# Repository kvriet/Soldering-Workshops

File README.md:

# Soldering Workshops

1. Wireless LEDs

2. Lighthouse

3. Moduli

4. LED cube

5. Lotus

6. Controller

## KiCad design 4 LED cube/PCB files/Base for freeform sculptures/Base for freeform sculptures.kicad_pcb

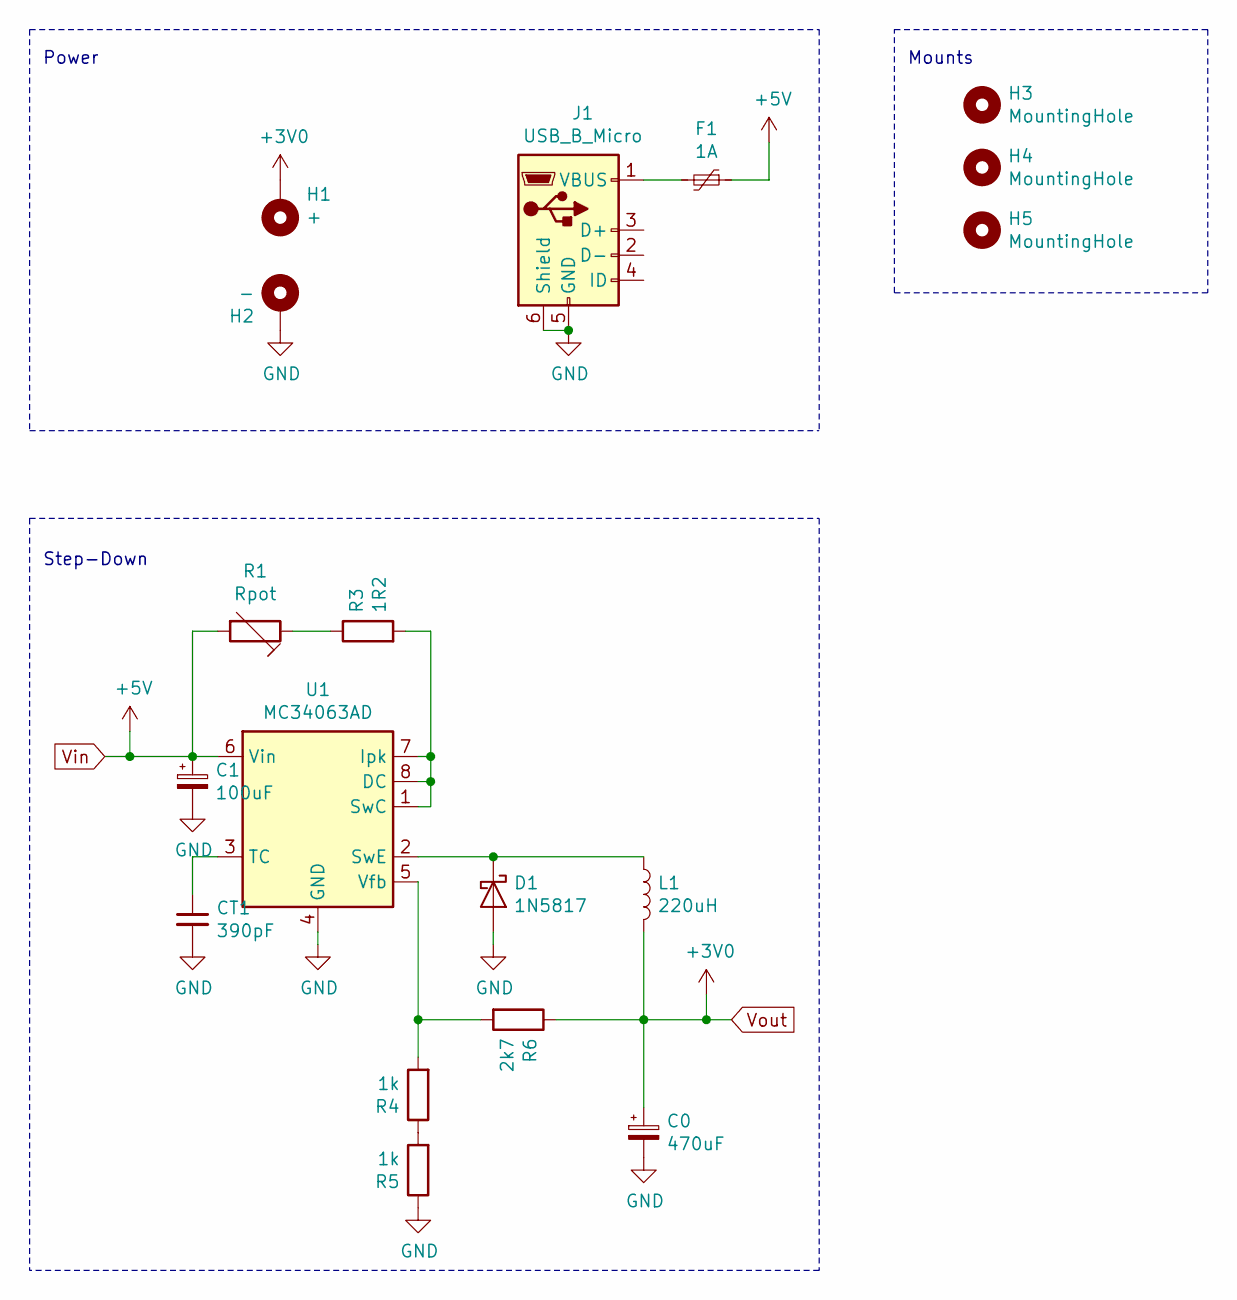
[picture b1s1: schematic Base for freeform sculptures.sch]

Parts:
C0: 470uF; CP_Radial_D10.0mm_P5.00mm
C1: 100uF; CP_Radial_D6.3mm_P2.50mm
CT1: 390pF; C_Disc_D4.3mm_W1.9mm_P5.00mm
D1: 1N5817; D_A-405_P10.16mm_Horizontal
F1: 1A; Fuse_Littelfuse_395Series
H1: +; Pin_D1.0mm_L10.0mm
H2: -; Pin_D1.0mm_L10.0mm
H3, H4, H5: MountingHole; Pin_D1.0mm_L10.0mm
J1: USB_B_Micro; USB_Micro-B_MC-026
L1: 220uH; L_Radial_D7.5mm_P5.00mm_Fastron_07P
R1: Rpot; Potentiometer_Bourns_3386P_Vertical
R3: 1R2; R_Axial_DIN0207_L6.3mm_D2.5mm_P10.16mm_Horizontal
R4, R5: 1k; R_Axial_DIN0207_L6.3mm_D2.5mm_P10.16mm_Horizontal
R6: 2k7; R_Axial_DIN0207_L6.3mm_D2.5mm_P10.16mm_Horizontal
U1: MC34063AD; DIP-8_W7.62mm_Socket_LongPads

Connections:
GND: C0.2, C1.2, CT1.2, D1.2 (A), H2.1, J1.5 (GND), J1.6 (Shield), R5.1, U1.4 (GND)
unnamed: CT1.1, U1.3 (TC)
unnamed: D1.1 (K), L1.1, U1.2 (SwE)
unnamed: F1.2, J1.1 (VBUS)
unnamed: R1.1, R3.1
unnamed: R3.2, U1.1 (SwC), U1.7 (Ipk), U1.8 (DC)
unnamed: R4.1, R5.2
unnamed: R4.2, R6.2, U1.5 (Vfb)
Vin: C1.1, F1.1, R1.2, U1.6 (Vin)
Vout: C0.1, H1.1, L1.2, R6.1

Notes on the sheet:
Power
Mounts
Step-Down

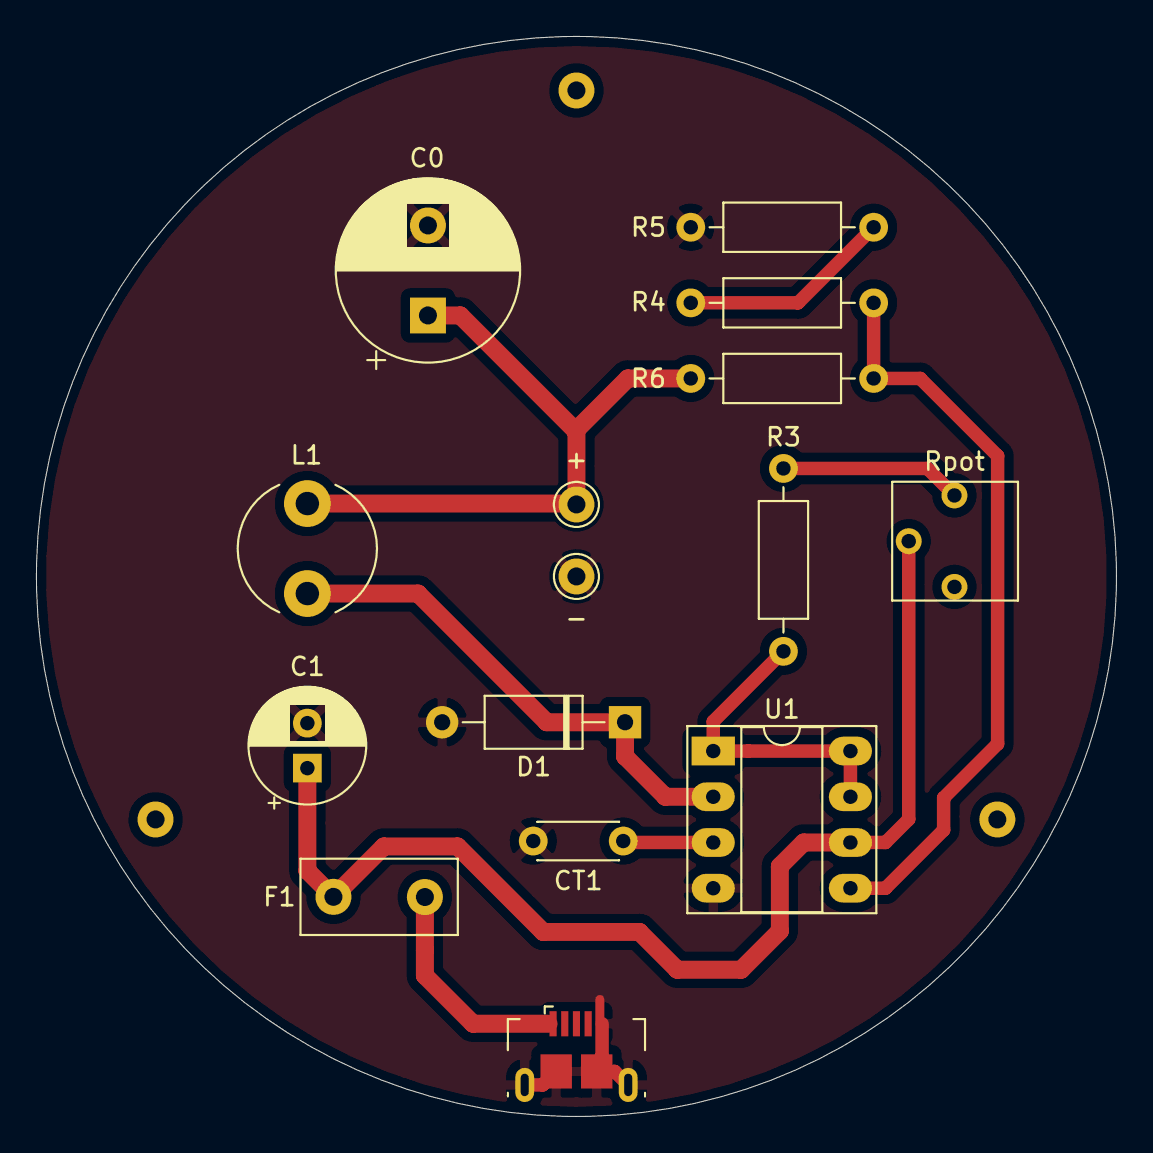
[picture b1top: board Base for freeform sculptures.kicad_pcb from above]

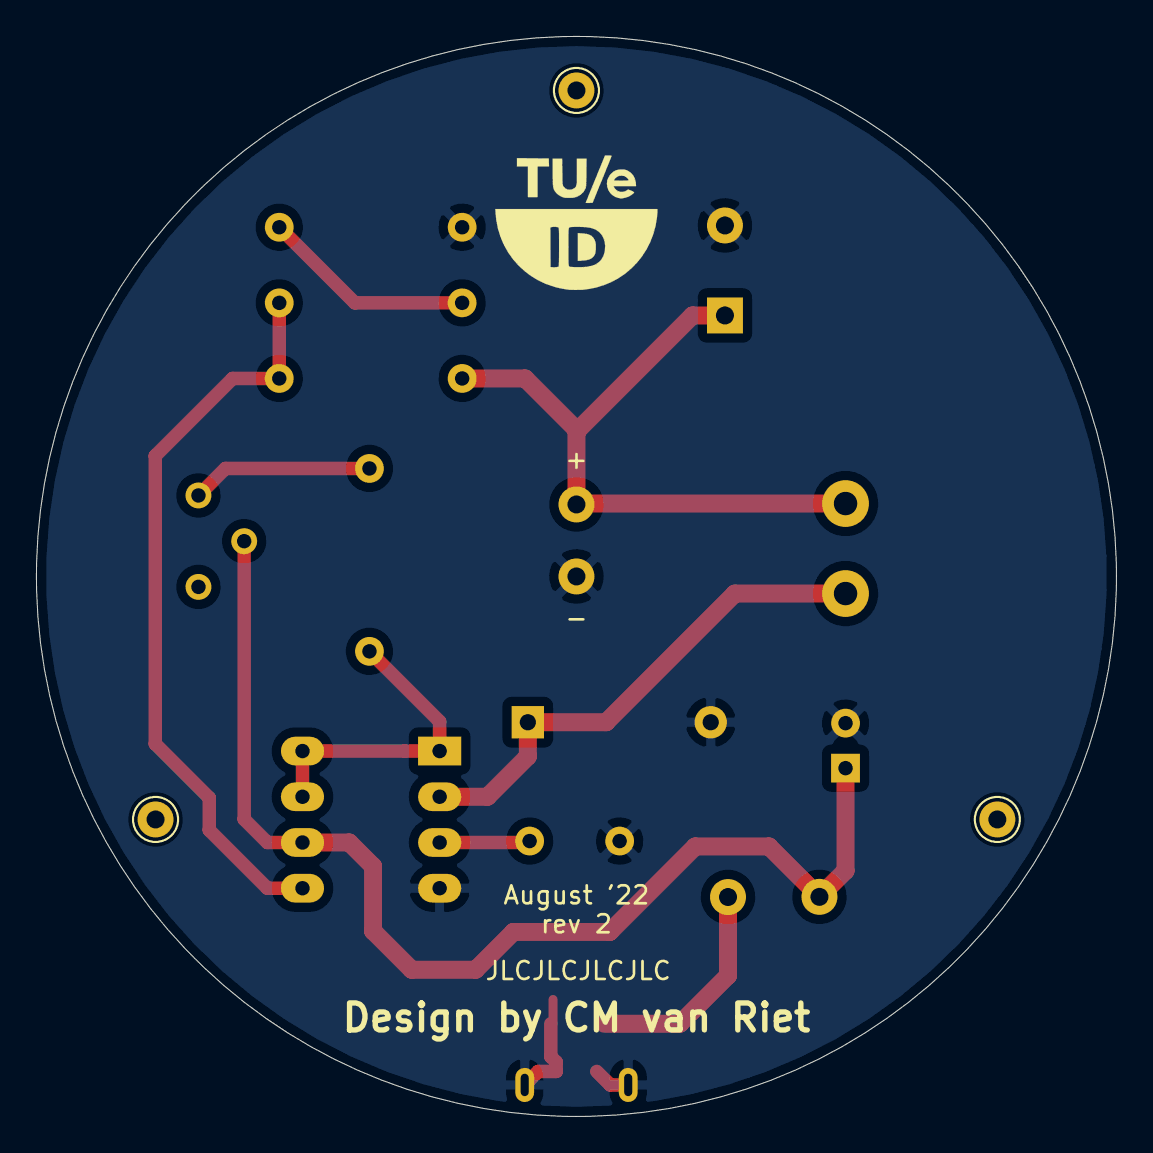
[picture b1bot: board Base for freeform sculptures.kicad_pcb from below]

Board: 2 copper layers, 60.0 x 60.0 mm, 18 parts (3 on the bottom side), 10 nets.

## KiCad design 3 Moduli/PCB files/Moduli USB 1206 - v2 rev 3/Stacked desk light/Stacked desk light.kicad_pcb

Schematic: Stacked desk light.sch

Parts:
D1: LED; LED_1206_3216Metric_Pad1.42x1.75mm_HandSolder
F1: Polyfuse_Small; LED_1206_3216Metric_Pad1.42x1.75mm_HandSolder
H1, H2: Hex_Conn; Conn_hex
J1: USB_B_Micro; USB_Micro-B_MC-026
R1: 150R; R_1206_3216Metric_Pad1.42x1.75mm_HandSolder
SW1: SW_DIP_x01; SW_CuK_OS102011MA1QN1_SPDT_Angled

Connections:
+5V: H1.7, H2.7, R1.2, SW1.1
GND: D1.1 (K), H1.1, H1.2, H1.3, H1.4, H1.5, H1.6, H2.1, H2.2, H2.3, H2.4, H2.5, H2.6, J1.5 (GND), J1.6 (Shield)
unnamed: D1.2 (A), R1.1
unnamed: F1.1, SW1.2
unnamed: F1.2, J1.1 (VBUS)

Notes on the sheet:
Power
Connectors
Light

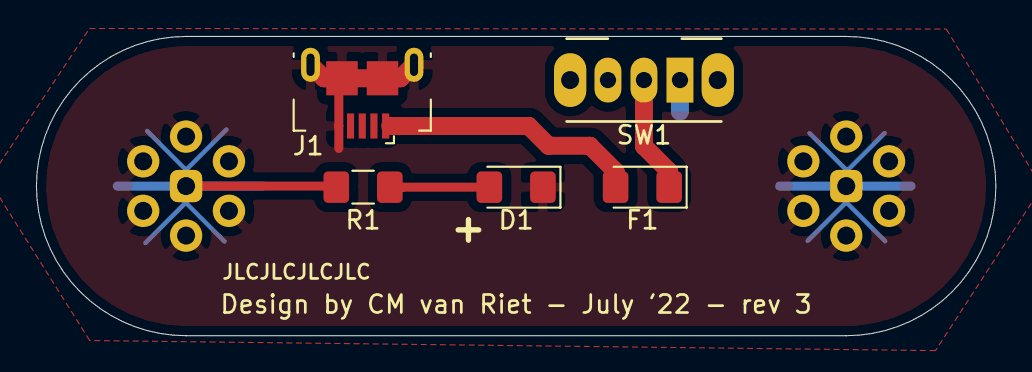
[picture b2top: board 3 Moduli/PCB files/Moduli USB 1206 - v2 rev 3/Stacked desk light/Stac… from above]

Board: 2 copper layers, 53.3 x 16.6 mm, 7 parts (0 on the bottom side), 5 nets.

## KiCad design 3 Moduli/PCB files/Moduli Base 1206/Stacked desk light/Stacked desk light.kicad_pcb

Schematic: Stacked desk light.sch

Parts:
D1: LED; LED_1206_3216Metric_Pad1.42x1.75mm_HandSolder
H1, H2: Hex_Conn; Conn_hex
R1: 150; R_1206_3216Metric_Pad1.42x1.75mm_HandSolder

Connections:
+5V: H1.7, H2.7, R1.2
GND: D1.1 (K), H1.1, H1.2, H1.3, H1.4, H1.5, H1.6, H2.1, H2.2, H2.3, H2.4, H2.5, H2.6
unnamed: D1.2 (A), R1.1

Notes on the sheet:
Connectors
Light

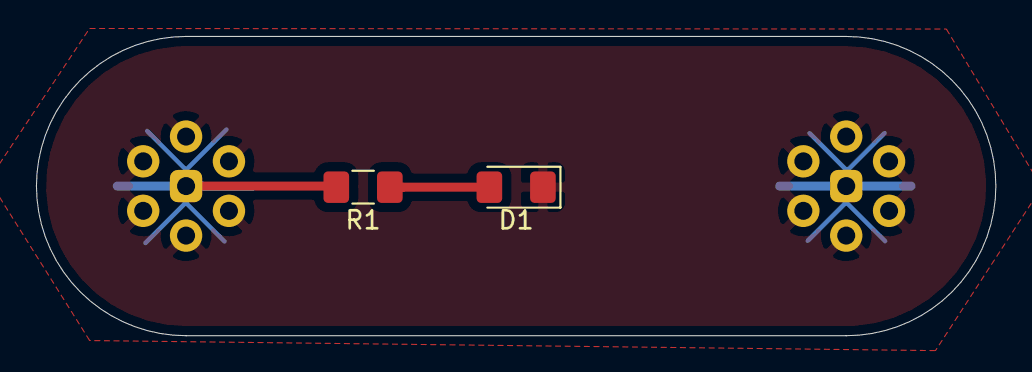
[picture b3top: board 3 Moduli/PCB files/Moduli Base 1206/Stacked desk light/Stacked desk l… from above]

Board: 2 copper layers, 53.3 x 16.6 mm, 4 parts (0 on the bottom side), 3 nets.

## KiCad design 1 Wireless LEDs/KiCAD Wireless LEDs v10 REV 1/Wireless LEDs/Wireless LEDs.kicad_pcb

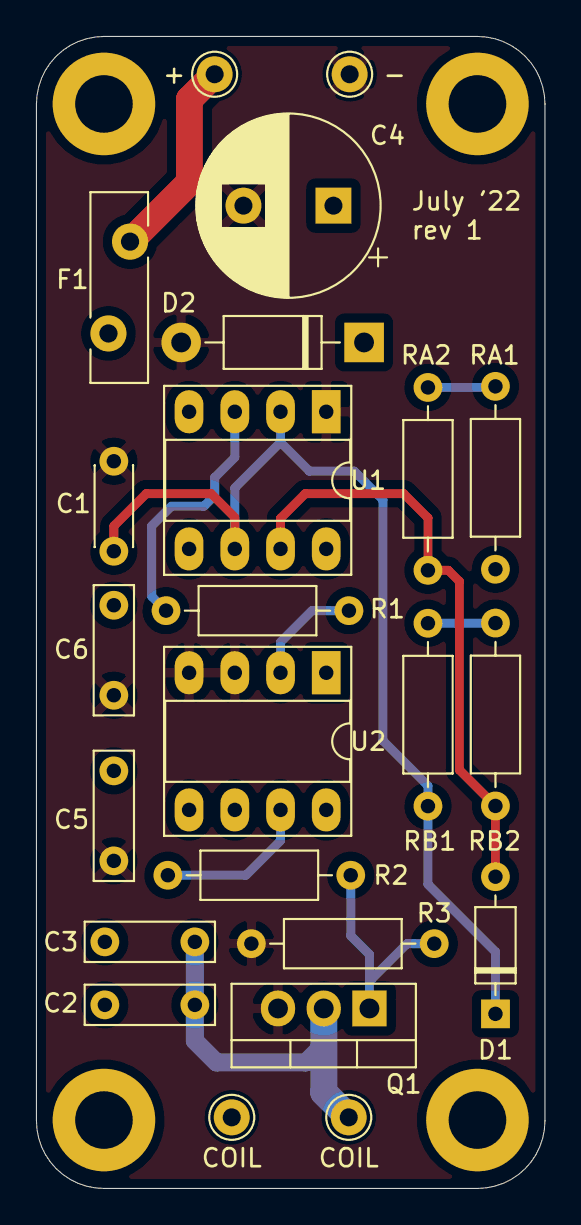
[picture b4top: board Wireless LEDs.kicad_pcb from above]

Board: 2 copper layers, 28.2 x 64.0 mm, 23 parts (0 on the bottom side), 12 nets.

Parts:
+: MountingHole_Pad; Pin_D1.0mm_L10.0mm
-: MountingHole_Pad; Pin_D1.0mm_L10.0mm
C1: 0.1nF; C_Disc_D4.3mm_W1.9mm_P5.00mm
C2: 22nF; C_Rect_L7.0mm_W2.0mm_P5.00mm
C3: 33nF; C_Rect_L7.0mm_W2.0mm_P5.00mm
C4: 330uF; CP_Radial_D10.0mm_P5.00mm
C5, C6: 100nF; C_Rect_L7.0mm_W2.0mm_P5.00mm
COIL: MountingHole_Pad; Pin_D1.0mm_L10.0mm
COIL#2: MountingHole_Pad; Pin_D1.0mm_L10.0mm
D1: 1N4148; D_DO-35_SOD27_P7.62mm_Horizontal
D2: 1N4007; D_DO-41_SOD81_P10.16mm_Horizontal
F1: Polyfuse_Small; Fuse_Bourns_MF-RG500
Q1: IRF740; TO-220-3_Vertical
R1, R2: 1k; R_Axial_DIN0207_L6.3mm_D2.5mm_P10.16mm_Horizontal
R3: 10k; R_Axial_DIN0207_L6.3mm_D2.5mm_P10.16mm_Horizontal
RA1: 2k7; R_Axial_DIN0207_L6.3mm_D2.5mm_P10.16mm_Horizontal
RA2: 12k; R_Axial_DIN0207_L6.3mm_D2.5mm_P10.16mm_Horizontal
RB1, RB2: 15k; R_Axial_DIN0207_L6.3mm_D2.5mm_P10.16mm_Horizontal
U1: LMC555xN; DIP-8_W7.62mm_Socket_LongPads
U2: TC4426; DIP-8_W7.62mm_Socket_LongPads

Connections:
+5V: C2.1, C3.1, C4.1, C5.1, C6.1, COIL#2.1, D2.1, F1.1, RA1.1, U1.4, U1.8, U2.6
GND: -.1, C1.2, C4.2, C5.2, C6.2, D2.2, Q1.3, R3.2, U1.1, U2.3, U2.4
unnamed: C1.1, D1.1, RB2.2, U1.2, U1.6
unnamed: C2.2, C3.2, COIL.1, Q1.2
unnamed: D1.2, RA2.2, RB1.1, U1.7
unnamed: +.1, F1.2
unnamed: Q1.1, R2.2, R3.1
unnamed: R1.1, U1.3
unnamed: R1.2, U2.2
unnamed: R2.1, U2.7
unnamed: RA1.2, RA2.1
unnamed: RB1.2, RB2.1

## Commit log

2022-09-27 Auto stash before rebase of "origin/main"
2022-09-28 added workshop costs and directories
2022-09-28 added moduli files
2022-09-28 Update README.md
    added pictures
2022-09-28 Update README.md
    added picture, fixed layout
2022-09-28 Auto stash before rebase of "origin/main"
    added design files
2022-09-28 added Lotus photo
2022-09-28 added wireless LED photo
2022-10-14 Update README.md
    changed led cube photo
2022-10-18 added manual Wireless LEDs
2022-10-25 updated Wireless LED workshop component specification
2022-11-06 updated parts list
2022-11-27 Updated manual
2022-12-20 Added Controller workshop to costs
2022-12-24 Updated workshop costs
2023-01-27 Added controller files
2023-01-27 Updated pin numbers
2023-01-28 Controller update and workshop cost update
2023-02-21 Controller workshop update
    updated manual, code.py and added HID library
2023-02-25 Added another spacer length
